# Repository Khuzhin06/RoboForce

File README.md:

# RoboForce

Всем привет! Давно хотели собрать своего робота? Не слышали про ROS? Не знаете с чего начать?

Тогда вы не зря зашли к нам, мы постараемся максимально подробно и быстро рассказать о нашем пути создания робота на ROS2 Jazzy и esp32,по этим материалам вы с легкостью сможете повторить этот проект. 

Ну а если вы хотите с головой погрузится в мир увлекательной робототехники и разобраться во всех тонкостях, то проходите курс на stepik - https://stepik.org/course/221157/syllabus Все материалы, используемые в этой статье были взяты из этого курса и мы лишь делимся опытом создания робота и проблемами с которыми столкнулись мы. 

Проблемы при сборки робота - это неотъемлемая часть процесса, поэтому мы постарались описать решение всех проблем с которыми мы сталкивались в процессе сборки и программирования робота.

Также много интересной, полезной и актуальной информации можете найти в нашем TG-канале https://t.me/RoboForc 

# Содержание:

[I модуль - Сборка робота](#i-модуль---сборка-робота)
- [1. Подготовка материалов и инструментов](#1-подготовка-материалов-и-инструментов)
- [2. Изготовление корпуса](#2-изготовление-корпуса)
  - [Шаг 1: Резка деталей](#шаг-1-резка-деталей)
  - [Шаг 2: 3D-печать](#шаг-2-3d-печать)
  - [Шаг 3: Сборка каркаса (первый слой)](#шаг-3-сборка-каркаса-первый-слой)
  - [Шаг 4: Сборка каркаса (средний слой)](#шаг-4-сборка-каркаса-средний-слой)
  - [Шаг 5: Соединение нижней и средней платформ](#шаг-5-соединение-нижней-и-средней-платформ)
  - [Шаг 6: Тестовый запуск](#шаг-6-тестовый-запуск)  

[II Модуль - Программировоние ESP32](#ii-модуль-программирование-esp32)
- [1. Настройка моторов](#1-настройка-моторов)
- [2. Загрузка основной программы на ESP32](#2-загрузка-основной-программы-на-esp32)  

[III Модуль - Настройка и программирование верхнего уровня](#iii-модуль-настройка-и-программирование-верхнего-уровня)
- [1. Установка ubuntu](#1-установка-ubuntu)
- [2. Установка ROS2](#2-установка-ros2)
- [3. Настройка необходимых пакетов](#3-настройка-необходимых-пакетов)

# I Модуль - Сборка робота

## 1. Подготовка материалов и инструментов
Необходимые инструменты:
- Лазерный резак – для резки фанеры
- Дрель и сверла (2–3мм) – для отверстий
- Набор отверток с разными насадками
- Паяльник (40 Вт) + припой (POS-60) – для электроники
- Мультиметр – проверка цепей
- Наждачка - для обработки краёв деталей после резки.

Материалы и комплектующие:  

| Компонент | Описание | Кол-во | Ссылка | Стоимость |
| ------- | ------- | ------- | ------- |------- |
| Фанера | Толщина 6 мм, 600х600 | 1 лист | https://www.ozon.ru/product/fanera-9-mm-sort-3-3-600h600-mm-1869700011/?at=PjtJzQPQXcWjXyvmIxmY3MwS95o8Lzcq71D1mFPGRX8v&from_sku=1901529745&oos_search=false | 370 |
| Винты М3 (+ гайки М3)| 30шт х 20мм, 4шт х 30мм, 4шт х 50мм | 38 | https://aliexpress.ru/item/1005005552471765.html?sku_id=12000033513521183&spm=a2g2w.productlist.search_results.15.7c287835NR6JBS | 160 |
| Винты М2.5 (+ гайки М2.5) | 2шт х 10мм | 2 | https://aliexpress.ru/item/1005005552471765.html?sku_id=12000033513521145&spm=a2g2w.productlist.search_results.15.7c287835NR6JBS | 150 |
| Винты М2 (+ гайки М2)| 4 шт х 10мм | 4 | https://aliexpress.ru/item/1005005552471765.html?sku_id=12000033513521113&spm=a2g2w.productlist.search_results.15.7c287835NR6JBS | 120 |
| Муфты  | Необходимы для закрепления колес на валах моторов | 2 | https://aliexpress.ru/item/1005004333022107.html?sku_id=12000028792464891&srcSns=sns_More&businessType=ProductDetail&spreadType=socialShare&tt=MG&utm_medium=sharing | 420 |
| OMNI-колесо | Позволяет двигаться роботу в любом направлении ьез поворота основных колес | 1 | https://aliexpress.ru/item/1005008405743640.html?sku_id=12000045061747881&spm=a2g2w.productlist.search_results.11.5e415abdiln3SR | 1540 |
| Микрокомпьютер Raspberry pi 5 8gb | «Верхний уровень». Обрабатывает информацию, поступающую с ESP (“нижнего уровня»). Поддержка новейших интерфейсов. Отлично подходит к задачам компьютерного зрения, обработки данных с лидаров.  | 1 | https://sl.aliexpress.ru/p?key=0vxkGbg | 10000 |
| Микроконтроллер ESP32-WROOM-32 | «Нижний уровень». Собирает информацию с датчиков, энкодеров и отправляет на «верхний уровень». Подходит для сетевого проекта из-за встроенных Wi-Fi и Bluetooth, высокой производительности и большого объёма памяти. | 1 | https://sl.aliexpress.ru/p?key=7oxkGZr | 300 |
| Моторы JGA25-370 77 RPM 12 B | Необходимы для передвижения робота. Используем 12В для упрощения питания. | 2 | https://aliexpress.ru/item/1005007793208347.html?sku_id=12000042220805718&spm=a2g2x.productlist.search_results.1.2ccd33e3p7kOox | 1200 |
| Драйвер моторов L298N | Необходим для управления моторов. | 1 | https://aliexpress.ru/item/1005007125159518.html?sku_id=12000042919988210&srcSns=sns_More&businessType=ProductDetail&spreadType=socialShare&tt=MG&utm_medium=sharing | 150 |
| Понижающие DC-DC преобразователи Readytosky FPV RC UBEC 5V 5A | Обеспечивает стабильное питание для микроконтроллера, микрокомпьютера, датчиков и драйверов. Имеет удобный форм-фактор и изолированный корпус. | 2 | https://aliexpress.ru/item/33019505937.html?sku_id=67198302173&srcSns=sns_More&businessType=ProductDetail&spreadType=socialShare&tt=MG&utm_medium=sharing | 530 |
| Литиевые батареи JOUYM 18650, 2000 мАч | Обеспечивает питание робота. Обладают высокой плотностью энергии при относительно небольшом размере. Можно последовательно соединять несколько штук, добиваясь нужного напряжения. | 3 | https://sl.aliexpress.ru/p?key=ajxkGkw | 460 |
| Держатель для батарей | Корпус для уставноки литейных батареек | 1 | https://aliexpress.ru/item/1005005586103501.html?sku_id=12000033652145033&spm=a2g2w.productlist.search_results.2.476f1d1frrOOTL | 140 |
| Лидар SLAMTEC RPLIDAR C1 | «Глаза» робота, который смотрит на окружение, вычисляет расстояние на 360 градусов вокруг, определяет препятствия впереди | 1 | https://sl.aliexpress.ru/p?key=fmxkGwR | 6740 |
| Штыревые штекеры и гнезда | Служат для удобства работы с микроконтроллером, его легкой замены - провода припаиваются не к самому МК, а к штекерам. | 2х2 | https://aliexpress.ru/item/1005004954771161.html?spm=a2g2x.detail.rcmdprod.7.6d172dc9ZId1M8&mixer_rcmd_bucket_id=UnknownMixerAbId&pdp_trigger_item_id=0_1005005576560025&ru_algo_pv_id=f712b2-61b690-22faee-72e977-1743876000&scenario=aerSimilarItemPdpRcmd&sku_id=12000031142220245&traffic_source=recommendation&type_rcmd=core | 200 |
| Комплект разъемов | Нужны для соединения электронной схемы без пайки. | 1 | https://aliexpress.ru/item/1005007622670523.html?sku_id=12000041540582736&spm=a2g2w.productlist.search_results.10.2e79633bJ9Bw1E | 120 |

СТОИМОСТЬ КОМПОНЕНТОВ ДЛЯ СБОРКИ РОБОТА:

За относительно небольшой бюджет можно также собрать достаточно надежного и производительного робота.
Суммируя все цены комплектующих из I модуля 1 пункта, мы получаем итоговую стоимость нашей модели - 22.600 рублей (на момент 06.04.2025).

## 2. Изготовление корпуса

### Шаг 1: Резка деталей
Загрузите DXF-файлы в станок лазерной резки.  
Основные детали:
- Основание (нижняя платформа)
- Средняя платформа
- Крышка (верхняя платформа)
- 2 опоры для OMNI колеса
- 5 стоек по 60 мм
- 4 стойки по 130 мм
После резки обработайте края наждачкой, чтобы избежать заусенцев.  

### Шаг 2: 3D-печать
Загрузите stl-файлы в станок 3D-печати.  
Основные детали:  
- 2 колеса
- Стойки для моторчиков

### Шаг 3: Сборка каркаса (первый слой)
1. Установка мотор редукторов
На валы мотор-редукторов установите колёса с помощью муфт (2 шт) и винтов М3 (2 шт), закрепите их стопорными винтами.

Найдите на нижней платформе посадочные места под моторы.
Зафиксируйте каждый мотор винтами M3 х 50 мм (4 шт) и гаек М3 (4 шт) с помощью напечатанных стоек (обратите внимание на то, чтобы провода от энкодеров были выведены к центру платформы)
Убедитесь, что при вращении колёса не задевают за край платформы и установлены ровно.
Уделите внимание ровной установке колес, это обеспечит качественное движение без лишних корректировок.

2. Установка OMNI колеса 
Найдите на нижней платформе посадочные места под вырезанные опоры OMNI колеса.
Установите их с помощью винтов М3 х 20 (4 шт) и гаек М3 (4 шт)

Закрепите OMNI колесо винтами М3 (2 шт).
Убедитесь, что при вращении колёсо не задевает за край платформы.

3. Установка драйвера моторов
Найдите в центре нижней платформы посадочные места под драйвер
Установите драйвер с помощью винтов М3 (2шт) и гаек М3 (2шт)

### Шаг 4: Сборка каркаса (средний слой)
1. Пайка шилда для ESP
Шилд – плата с контактными площадками.   
Установите на ESP штыревые гнезда, затем вставьте конструкцию в печатную плату (со стороны пайки)

Установите штыревые штекеры в средних с конструкцией линиях на плате.
Аккуратно переверните плату, поддерживая все компоненты.

Включите паяльник и дождитесь, пока инструмент разогреется до 300-350°C. 
Нанесите припой на крайние контакты (используйте флюс для лучшего растекания припоя)
Необходимо спаять все крайние контакты попарно (контакт гнезда с контактом штекера)
Проведите аналогичную работу со всеми оставшимися контактами (ВАЖНО: два спаянных контакты не должны быть соединены с соседними. 

После окончания пайки необходимо провести проверку: 
А. Визуальный осмотр:  
   - Нет ли перемычек между контактами (проверка на отсутствие короткого замыкания)
 Все ли дорожки пропаяны (особенно у штыревых разъёмов).  
Б.  Тест мультиметром:  
   - Прозвоните линии 5V и 3.3V на КЗ.  
   - Проверьте контакты GPIO на обрыв.

2. Установка шилда на платформу
Найдите на средней платформе посадочное место для шилда
Вставьте снизу в платформу винты М2 (4шт) и накрутите на них гайки М2 (4шт). Данная конструкция не позволит передать находящиеся под шилдом провода  
Установите на винты собранный шилд и закрепите его сверху гайками М2 (4шт)

3. Установка блока питания
Найдите на средней платформе посадочное место для блока питания (средняя часть платформы) 
Закрепите блок с помощью винтов М3 (2 шт) и гаек М3 (2шт)  (ВАЖНО: провода должны выходить в центральную часть платформы)

4. Монтаж:
   макетную и монтажную схему можно подробно изучить в папке Electronic scheme
Электрическая схема:

Пайка проводов, преобразователей, RGB ленты, драйвера, энкодеров, микроконтроллера.
Залудите контакты перед пайкой, а затем работайте по тому же принципу, как и при пайке шилда  
После окончания пайки необходимо провести проверку (визуальный осмотр и тест мультиметром) (ВАЖНО: проверьте, нет ли пережатых проводов)

### Шаг 5: Соединение нижней и средней платформ
Соберите стойки из фанеры: 5 штук по 60 мм, 4 штуки по 130 мм (для этого понадобятся гайки М3 18 шт)
Соедините нижнюю и верхнюю платформы с помощью стоек по 60 мм, винтов М3 (10шт)

### Шаг 6: Тестовый запуск
- Подключите питание. 
- Проверьте работу моторов, питание и загрузку ESP.
- Проанализируйте, движится ли робот в заданном вами направлении или нет.
ВАЖНО: есть вероятность, что робот поедет в обратную сторону, так как у него 2 шнура, которые можно перепутать местами. В таком случае необходимо поменять местами номера бортов в коде и загрузить его. Теперь робот поедет в заданном вами направлении.
- Измерьте количество тиков и запишите их в программу.

# II Модуль - Программирование ESP32

После того как вся аппаратная часть собрана, можно переходить и к программной.
Все действия лучше делать на ноутбуке - так как это будет быстрее и надежней, хотя в теории можете и сделать все тоже самое на raspberry.
Начнем с программирования "нижнего уровня", тоесть esp32. Программировать будем через arduino IDE (если она еще у вас не установлена, то можете скачать с официального сайта https://www.arduino.cc/en/software ).
Чтоб можно было прошивать нашe платe добавим ее в список доступных для прошивки. Нужно зайти в файл->настройки и в поле "Дополнительные менеджеры плат" вставляем ссылку: https://raw.githubusercontent.com/espressif/arduino-esp32/gh-pages/package_esp32_index.json и нажимаем "ОК". 
После заходим в инструменты->плата->менеджер плат тут в строке поиска вводим esp32, выбираем соответсвующий вариант снизу и нажимаем на кнопку установить. 
После всех этих процедур для прошивки станут доступны платы семейства  ESP32.  Чтоб выбрать нужную плату заходим в инструменты->esp32 и выбираем нужную плату (мы использовали "ESP32 dev Module"). Также необходимо подключить саму плату к компьютеру и выбрать порт к которому она подключена заходим опять в инструменты->порт и выбираем нужный порт.
Помимо этого необходимо установить библиотеку для адресной светодиодной ленты. Для этого заходим в скетч->подключить библиотеку->Управлять библиотеками в поле поиска вводим "neopixel" и выбираем Adafruit neopixel и нажимаем установить.

## 1. Настройка моторов

Здесь нам нужно понять как подключены моторы и сделать так, чтоб робот ехал вперед, когда мы действительно этого хотим.

-проверить направление вращения моторов
-проверить подключение энкодеров

Скачиваем или копируем код для esp32 из папки low_level "test_move_esp32", открфываем этот код в arduino ide и нажимаем в правом верхнем углу "загрузить".

После полной загрузки кода колеса робота должны вращаться вперед, если это не так, то следует поменять в коде местами номера пинов, к которым подключён драйвер моторов левой или право стороны.
Для определения вращения энкодеров открываем в arduino IDE serial port и следим за значениями: оба значения на левом и правом моторах должны возрастать, если это не так, то меняем местами пины энкодера в программе.

## 2. Загрузка основной программы на ESP32.

Для этого шага нам необходимо скопировать все параметры из прдыдущего кода, а также измерить диаметр колеса и расстояние между центрами колёс.
Все эти параметры вашего робота необходимо внести в скетч main_esp32.ino, который находится в папке low-level. Этот код вы также скачиваете (или копируете) и открываете в Arduino IDE для дальнейшей прошивки. После внесения всех изменений в вашу программу по аналогии с 1 шагом загружаем программу на  микроконтроллер.

# III Модуль - Настройка и программирование верхнего уровня

До запуска робота остался последний и самый ответственный шаг. Настройка микрокомпьютера - наших "мозгов" робота. В нашем проекте эту роль выполняла raspberry pi 5 8gb, поэтому советуем все повторять на таком же железе для предотвращения проблем. Безусловно, подойдет и другое железо, по типу repka pi, orange pi, banana pi и подобных "фруктов". Но наиболее популярной и поддерживаемой всетаки остается "малинка".

## 1. Установка ubuntu

По сути raspberry pi является аналогом вашего ноутбука или настольного компьютера, но куда меньших размеров и, скорее всего, хуже по вычислительным мощностям. Но тем не менее нам нужно поставить на наш микрокомпьютер операционную систему - наиболее подходящая ubuntu 24.04. !!! при сборке нашего робота мы сначала поставили 24.10 - по принципу: больше - лучше, но тут,увы, так не работает. И чтобы у вас без проблем все встало как нужно необходимо использовать именно ubuntu 24.04 LTS!!! 
Скачать ее можно с официального сайта - она абсолютно бесплатная. После загрузки образа диска необходимо его записать на sd карту, которая будет стоять в малинке. Мы использовали на 64гб. Или же можно сразу скачать Raspberry PI Imager(https://www.raspberrypi.com/software/) и там уже в интерфейсе выбрать нужную операционную систему и ваш носитель.

## 2. Установка ROS2

После установки и базовых настроек операционной системы можно установить и сам ros2 jazzy (в нашем проекте используется десктопная версия ros-jazzy-desktop), лучше всего брать команды для установки с официального сайта (https://docs.ros.org/en/jazzy/Installation/Ubuntu-Install-Debs.html), так как они могут меняться. 

Если установить не получается пробуем еще раз, внимательно копируем все и вставляем в терминал. Если совсем не помогает, то можно попытаться погуглить ошибку, которую вам выдает терминал или же переустановить заново операционку на флешку и убедится что это точно ubuntu 24.04 LTS.

Также установим еще пару пакетов:

```
sudo apt install python3-pip
```

```
pip3 install setuptools
```

```
sudo apt install python3-colcon-common-extensions
```

## 3. Настройка необходимых пакетов

После установки ros2 в домашнеq директории нужно создать папку где будут хранится все наши пакеты для ros2.

```
mkdir ros2_ws
```

```
cd ros2_ws
```

```
mkdir src
```

```
cd-
```

```
colcon build
```

после создания нашего рабочего пространства
создадим пакет, который будет считывать сообщения из топика /cmd_vel

```
cd ~/ros2_ws/src
ros2 pkg create robot_control --build-type ament_python --dependencies rclpy geometry_msgs
cd robot_control/robot_control
```

создаем файл robot_controller_node.py и копируем в него код из одноименного файла папки high_level. Предварительно также нужно подключить прошитую esp32 к одному из портов raspberry pi, а затем ввести команду: 
```
ls -l /dev/serial/by-path/
```

после необходимо скопировать путь и заменить его в коде.
сохраняем файл. Делаем скрипт исполняемым:
```
chmod +x robot_controller_node.py
```

Далее находим и редактируем файл setup.py в этом пакете (нужно добавить 3-ю строчку):

```
entry_points={
    'console_scripts': [
        'robot_controller_node = robot_control.robot_controller_node:main',
    ],
},
```

Затем пересоберем наш пакет и установим все зависимости:

```
cd ~/ros2_ws
colcon build
source install/setup.bash
```

И запускаем наш пакет:

```
ros2 run robot_control robot_controller_node
```

Проверяем список топиков в другом терминале, должен появиться топик /cmd_vel

```
source /opt/ros/jazzy/setup.bash
ros2 topic list
```

Если топик появился, то все прошло успешно и мы можем управлять нашим роботом с клавиатуры!

Для этого установим пакет:

```
sudo apt install ros-jazzy-teleop-twist-keyboard
```
И запускаем пакет: 
```
ros2 run teleop_twist_keyboard teleop_twist_keyboard
```
Теперь робот должен ехать! Поздравляю мы проделали большой путь и запустили робота!

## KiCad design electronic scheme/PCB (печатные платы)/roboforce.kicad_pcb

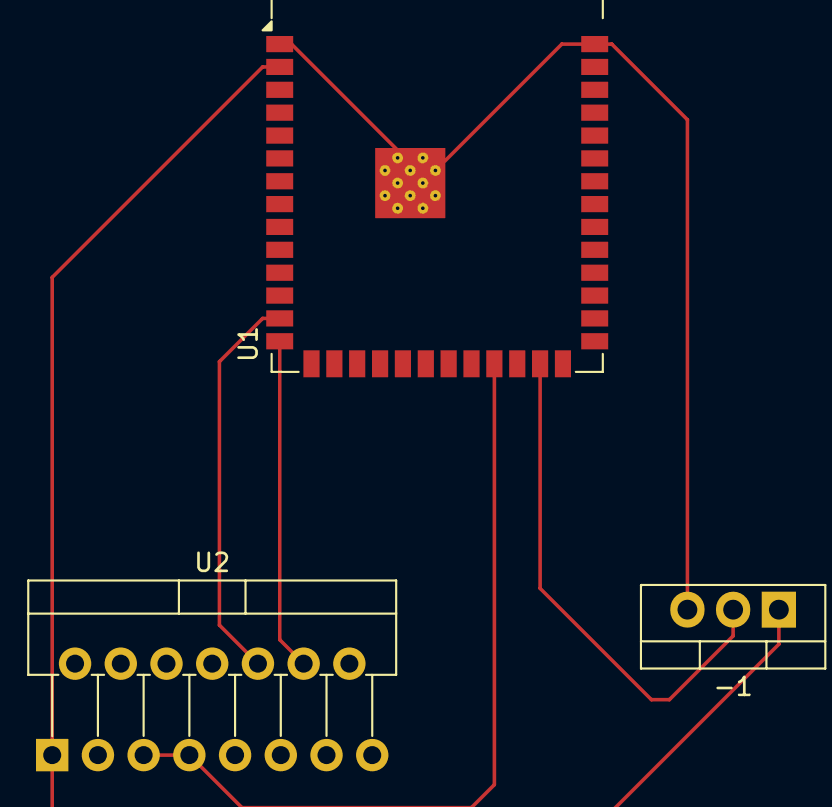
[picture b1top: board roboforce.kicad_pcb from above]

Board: 2 copper layers, 3 parts (0 on the bottom side), 6 nets.

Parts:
-1: -; TO-220-3_Vertical
U1: ESP32-S3-WROOM-1
U2: L298N; TO-220-15_P2.54x2.54mm_StaggerOdd_Lead4.58mm_Vertical

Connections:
unnamed: -1.3 (GND), U1.1 (GND), U1.40 (GND), U1.41 (GND)
unnamed: -1.1 (VA), U1.2 (3V3), U2.1 (SENSE_A)
unnamed: -1.2 (VB), U1.25 (IO48)
unnamed: U1.20 (IO12), U1.23 (IO21), U2.5 (IN1), U2.7 (IN2)
unnamed: U1.13 (IO19), U2.10 (IN3)
unnamed: U1.14 (IO20), U2.12 (IN4)

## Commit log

2025-04-05 Rename test_move_esrRos.ino to test_move_esз32.ino
2025-04-05 README.md
2025-04-05 Create test_move_esp32
2025-04-05 Rename photo_5444974429529565123_y.jpg to main_photo.jpg
